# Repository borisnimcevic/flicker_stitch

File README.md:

# Flicker Stitch — Assembly Instructions

Stitch a working circuit onto fabric. In this kit you sew small electronics
onto an embroidered badge using **conductive thread**, and when you flip the
switch, the LEDs light up.

By [@borisnotes](https://borisnotes.com)

---

## 1. What's in the bag

| # | Item | Qty |
|---|------|-----|
| 1 | Canvas | 1 |
| 2 | Design paper | 1 |
| 3 | Needle | 1 |
| 4 | Needle threader | 1 |
| 5 | Conductive thread | 1 |
| 6 | Outline thread (black) | 1 |
| 7 | Colour thread 1 | 1 |
| 8 | Colour thread 2 | 1 |
| 9 | Battery module with switch | 1 |
| 10 | Blinky LED module | 2 |
| 11 | Brooch pin | 1 |
| 12 | CR2032 coin cell | 1 |

> **Not in the bag, but useful:** good light, a flat table, a small pair of
> scissors, clear nail polish (optional, for sealing knots).

---

## 2. How the electronics work

Electricity needs a **loop**. It leaves one side of the battery, passes through
the parts, and comes back to the other side. If the loop is broken anywhere,
nothing lights up.

The circuit in this kit is just a battery, a switch and two blinky LEDs:

- **Battery (CR2032)** — the power source, 3 V. It has a **+** side and a
  **–** side.
- **Switch** — opens and closes the loop. Off means the loop is open.
- **Blinky LED modules (×2)** — each one has a tiny chip inside that turns its
  LED on and off by itself. They only work **one way round**: current must go
  in the **+** side and out the **–** side. The resistor that protects the LED
  is already on the module, so you don't need any extra parts.
- **Conductive thread** — the wires. Each line of stitching carries current
  from one pad to the next.

Follow the lines on the schematic:

1. From the battery **+**, current goes through the **switch**.
2. After the switch it reaches a junction (the top green dot) that feeds
   **both LEDs at once**. This is called wiring in *parallel*, so each LED gets
   the full battery voltage and blinks on its own.
3. Both LEDs return to the battery **–** through a second junction (the bottom
   green dot), which closes the loop.

### Two rules for the thread

1. **+ and – must never touch.** If two stitches from opposite sides of the
   battery touch, the current takes a shortcut and the LEDs stay dark (and the
   battery drains).
2. **Every joint needs contact.** The thread has to actually touch the metal
   pad, and be pulled snug against it.

### Where everything goes

The design paper in your bag shows this same layout.

The dashed lines are the conductive thread. The red **+** and **–** marks show
the polarity of each pad:

- The **battery module** sits on the left. Its top pad is **–** and its
  bottom pad is **+**.
- The two **blinky LED modules** sit in the alien's eyes. On each one, the
  top pad is **–** and the bottom pad is **+**.
- All the **–** pads are joined by one line of thread, and all the **+** pads
  are joined by another. The two lines never cross or touch.

---

## 3. Threading the needle

1. **Cut about 20 cm** of conductive thread. Longer is not better; it
   tangles and frays.
2. Thread the needle with the **needle threader** (see below). If the thread
   won't go, snip the end at a sharp angle to remove loose fibres. Wetting
   the tip helps.
3. Pull it through until you have about **2 cm** on the short side. This way
   you can hold it with the same fingers that hold the needle.
4. **Tie a knot** at the long end. This is the anchor that stops the thread
   pulling through.

### Tying the knot

1. Make a loop around your finger.
2. Roll the thread off your fingertip so it twists into a small coil.
3. Pinch the coil and pull the thread through to the end. A small, firm knot
   forms.
4. Snip off the tail, leaving ~3 mm.

> **Tip:** conductive thread is slippery. Make the knot a double knot.

### Using the needle threader

1. Push the wire loop of the threader through the eye of the needle.
2. Pass the end of the thread through the wire loop.
3. Pull the threader back out. The thread comes through the eye with it.

---

## 4. Running stitch: connecting the parts

A **running stitch** is the simplest stitch: the needle goes down, up, down,
up, in a dotted line. It's how you'll draw each "wire".

### Place the parts

Use the **design paper** (item 2) as your map. It shows where everything goes.

1. Lay the design paper next to the canvas, so you can compare them.
2. Put the **battery module** on the **back** of the canvas, on the left where
   the paper shows it. The coin cell holder must face the **edge** of the
   canvas. The switch is part of the module, so it goes along with it.
3. Put one **blinky LED module** in each of the alien's eyes.
4. Check the **+** and **–** marks against the polarity picture in section 2.
   The **–** pads are at the top and the **+** pads at the bottom.
5. Hold each part still with a finger while you stitch its first pad.

### The basic motion

1. Bring the needle **up** from the back of the fabric.
2. Take the needle **down**, a short distance ahead (3–5 mm).
3. Bring it **up** again, one stitch-length further.
4. Repeat. The thread shows as dashes on the front, and as longer dashes on
   the back.

Keep stitches small and even, and pull the thread **snug but not tight**, so the
fabric doesn't pucker.

### Stitching to a pad

1. Start with the knot on the **back**, near the first pad.
2. Bring the needle up through the **hole** in the pad.
3. Go back down through the same hole, then up again. Do this **2–3 times**,
   pulling snug each time. This wraps the thread on the metal for a solid
   contact.
4. Now run stitches along the path to the next pad, following the lines
   on the canvas.
5. At the next pad, wrap through the hole **2–3 times** again.

### Ending a thread

1. Finish with a wrap through the last pad.
2. Take the needle to the **back**, and tie a double knot close to the fabric.
3. Trim the tail, so it can't touch another line.

---

## 5. Test it

1. Push the **CR2032 coin cell** into the holder on the battery module, with
   the **+** side facing up.
2. Slide the switch to **ON**.
3. The LEDs should light or start blinking.

---

## 6. Back stitch: outlining with the black thread

The **black thread** is for decoration only: it draws the outline of the
alien's head, the eyes and the mouth. It does not carry electricity. Use a **back
stitch**, which makes a solid, unbroken line.

### Prepare the thread

1. Cut about **40 cm** of black thread. It is made of **6 thin strands** twisted
   together.
2. Hold the end and gently pull **one strand** out. Pull it slowly and let the
   other five slide free, so they don't knot.
3. Thread the needle with the single strand (use the needle threader again).
4. Pull the strand through until both ends are **the same length**. The thread
   is now doubled: the **needle is on the fold** at one end.
5. **Tie a knot** in the two loose ends together. Now you have a doubled thread
   with the needle on one end and the knot on the other.

### The back stitch

1. Bring the needle **up** from the back, one stitch-length ahead of where you
   want the line to start (**1**).
2. Take the needle **down** at the start of the line, going back to meet the
   previous stitch (**2**). This makes the first stitch.
3. Bring the needle **up** again, one stitch-length ahead of the last hole
   (**3**).
4. Take the needle **down** in the hole where the last stitch ended. Repeat,
   always stepping forward and then going back.

Keep the stitches short (about 2–3 mm) and the same size. Pull the thread snug
but not tight so the fabric doesn't pucker.

### Where to stitch

Follow the printed lines on the canvas: the outline of the alien's head, the
eyes and the mouth. The outline goes around the shapes, not over the electronics.

### Ending the thread

1. Take the needle to the **back**.
2. Pass it under a few stitches, and tie a knot close to the fabric.
3. Trim the tail.

---

## 7. Satin stitch: the technique

You will use **satin stitch** to fill in the eyes and mouth, colour in the
alien, and add the shading. It is many straight stitches laid side by side, so
that no fabric shows through. Practise the motion here first.

1. Bring the needle **up** from the back at one edge of the area you are
   filling.
2. Take the needle **down** at the opposite edge, straight across the shape.
3. Bring the needle **up** again right next to where you came up the first
   time, and go **down** right next to the last hole on the other side.
4. Repeat, laying each stitch tight against the one before it, until the area
   is covered.

Keep the stitches parallel and close together, and pull each one snug but not
tight so the fabric doesn't pucker.

### Cover the electronics

Stitch **over the LED modules and the grey conductive thread**. Cover
everything **except the LED light itself**, so that only the glow shows. Look at
the finished badge at the top of this page to see how it should look.

---

## 8. Filling the eyes and mouth

Once the black **outline** is finished, fill in the eyes and mouth with black
satin stitch. Use the **black thread** again, but this time with **2 strands**.

### Prepare the thread

1. Cut about **40 cm** of black thread.
2. Pull **2 strands** out together, slowly, and let the others slide free.
3. Thread the needle with the two strands, and pull them through until both
   ends are **the same length**. The thread is folded in half, with the
   **needle on the fold**.
4. **Tie a knot** in the loose ends. You are now stitching with **4 strands**
   (2 strands, doubled).

### Fill the shapes

1. Fill each eye and the mouth with satin stitch. Stitch right up to the
   outline.
2. In the eyes, the stitches go **over the LED module and the grey conductive
   thread**. Leave the **LED light itself uncovered**.
3. End the thread on the back: pass the needle under a few stitches, tie a
   knot close to the fabric, and trim the tail.

---

## 9. Colouring in the alien

Now fill the alien's head with colour, using **colour thread 1**. The colour
threads are for decoration only, like the black thread. Use the same **satin
stitch**.

### Prepare the thread

1. Cut about **40 cm** of colour thread. It is made of **6 thin strands**
   twisted together.
2. Pull **2 strands** out together, slowly, and let the other four slide free.
3. Thread the needle with the two strands (use the needle threader if you need
   it).
4. Pull the strands through until both ends are **the same length**. The
   thread is now folded in half, with the **needle on the fold**.
5. **Tie a knot** in the loose ends. You are now stitching with **4 strands**
   (2 strands, doubled).

### Fill the head

1. Fill the head with satin stitch, right up to the black outline and the
   filled eyes and mouth.
2. Cover any grey thread that still shows.
3. End the thread on the back: pass the needle under a few stitches, tie a
   knot close to the fabric, and trim the tail.

---

## 10. Shading with the second colour

Finish the picture by adding shading with **colour thread 2**. Use the same
**satin stitch** as in the last step.

1. Prepare a new thread exactly as before: about **40 cm**, 2 strands, folded
   in half, with a knot at the end.
2. Stitch satin stitches with colour thread 2 on the areas you want to shade.
   Make the stitches **different lengths** and slide them in **between** the
   colour 1 stitches, so the two colours blend into each other, as in the
   photo below.
3. Keep the stitches parallel and close together. Cover any grey thread that
   still shows, but leave the LED light uncovered.
4. End the thread on the back: pass the needle under a few stitches, tie a
   knot close to the fabric, and trim the tail.

Your badge is finished.

---

## 11. Optional: attach the badge

### As a brooch

1. Place the **brooch pin** on the back of the badge, near the top.
2. Prepare **black thread** as you did for the outline: 1 strand, folded in
   half, with a knot at the end.
3. Sew through each hole of the pin and the canvas with a few tight stitches.
4. Tie a knot on the back, and trim the tail.

### Or sew it onto something

You don't need the pin. Sew the badge straight onto a jacket, bag or other
garment with a running stitch around the edge of the canvas.

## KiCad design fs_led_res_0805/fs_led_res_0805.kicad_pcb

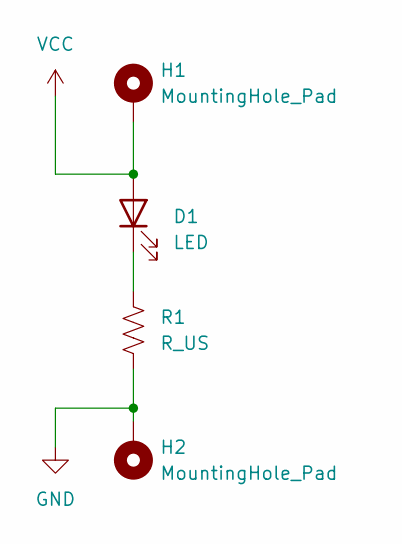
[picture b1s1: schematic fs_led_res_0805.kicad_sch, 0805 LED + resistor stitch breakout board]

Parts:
D1: LED; LED_0805_2012Metric_Pad1.15x1.40mm_HandSolder
H1, H2: MountingHole_Pad; MountingHole_2.2mm_M2_DIN965_Pad_TopBottom
R1: R_US; R_0805_2012Metric_Pad1.20x1.40mm_HandSolder

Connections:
GND: H2.1 (1_1), R1.2
unnamed: D1.1 (K), R1.1
VCC: D1.2 (A), H1.1 (1_1)

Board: 2 copper layers, 4 parts (1 on the bottom side), 3 nets, no tracks yet.

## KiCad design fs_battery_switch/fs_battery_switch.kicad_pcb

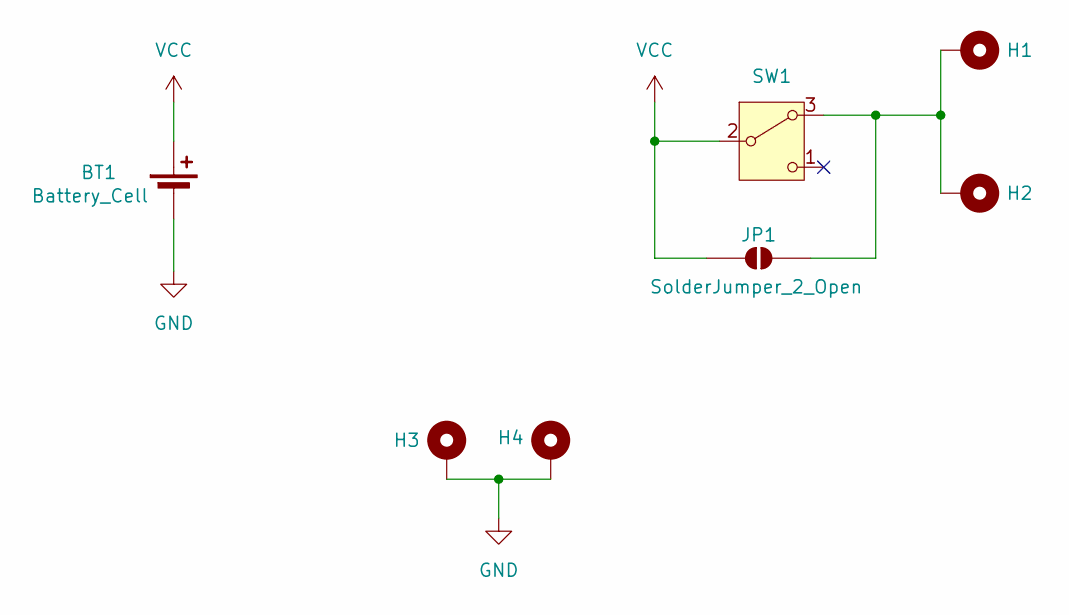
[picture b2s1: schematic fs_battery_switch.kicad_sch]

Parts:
BT1: Battery_Cell; BatteryHolder_MPD_BC2003_1x2032
H1, H2, H3, H4: MountingHole_Pad; MountingHole_2.2mm_M2_DIN965_Pad
JP1: SolderJumper_2_Open; SolderJumper-2_P1.3mm_Open_TrianglePad1.0x1.5mm
SW1: SW_Nidec_CAS-120A1; SW_SPDT_PCM12

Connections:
GND: BT1.2 (-), H3.1 (1_1), H4.1 (1_1)
unnamed: H1.1 (1_1), H2.1 (1_1), JP1.2 (B), SW1.3 (A)
VCC: BT1.1 (+), JP1.1 (A), SW1.2 (B)

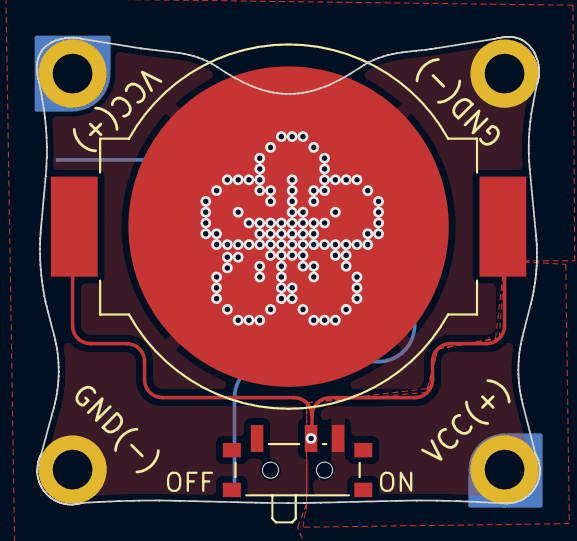
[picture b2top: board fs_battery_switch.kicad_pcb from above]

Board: 2 copper layers, 28.0 x 26.0 mm, 7 parts (1 on the bottom side), 3 nets.

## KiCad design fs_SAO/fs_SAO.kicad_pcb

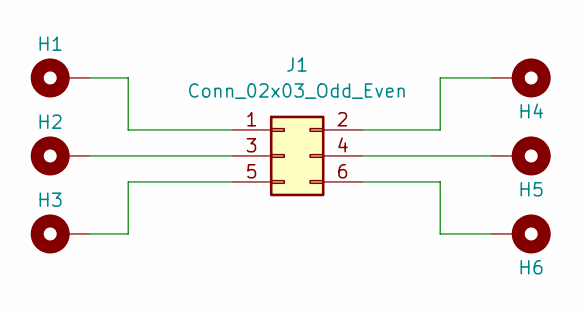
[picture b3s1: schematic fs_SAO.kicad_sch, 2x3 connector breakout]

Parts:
H1, H2, H3, H4, H5, H6: MountingHole_Pad; MountingHole_2.2mm_M2_Pad_TopBottom
J1: Conn_02x03_Odd_Even; IDC-Header_2x03_P2.54mm_Vertical_SMD

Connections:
unnamed: H1.1 (1_1), J1.1
unnamed: H4.1 (1_1), J1.2
unnamed: H2.1 (1_1), J1.3
unnamed: H5.1 (1_1), J1.4
unnamed: H3.1 (1_1), J1.5
unnamed: H6.1 (1_1), J1.6

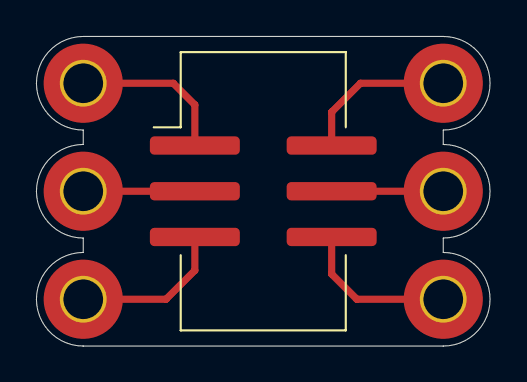
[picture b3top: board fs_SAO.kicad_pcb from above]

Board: 2 copper layers, 25.2 x 17.2 mm, 7 parts (0 on the bottom side), 6 nets.

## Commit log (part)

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2026-03-23 init project
2026-03-23 demo resistor
2026-03-24 reorganize the repo
2026-03-24 first draft of 0805 breakout board
2026-03-25 create panel
2026-03-25 init footprint for 0603
2026-03-25 resistor 0603 stitch breakout board
2026-03-25 add hand soldering pad
2026-03-25 make led + resistor 0603
2026-03-25 make led + resistor 0805
2026-03-25 add plus sign on resistor boards
2026-03-25 battery holder + switch
2026-03-25 battery + switch ordler panel
2026-03-25 resistor 0805 order
2026-03-26 resistor 0603 order
2026-03-26 order led res 0805
2026-03-26 order led res 0603
2026-03-26 order flex 0805 stitch breakout
2026-04-27 added 2x3 connector expander
